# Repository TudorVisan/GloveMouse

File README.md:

GloveMouse
==========

GloveMouse repository

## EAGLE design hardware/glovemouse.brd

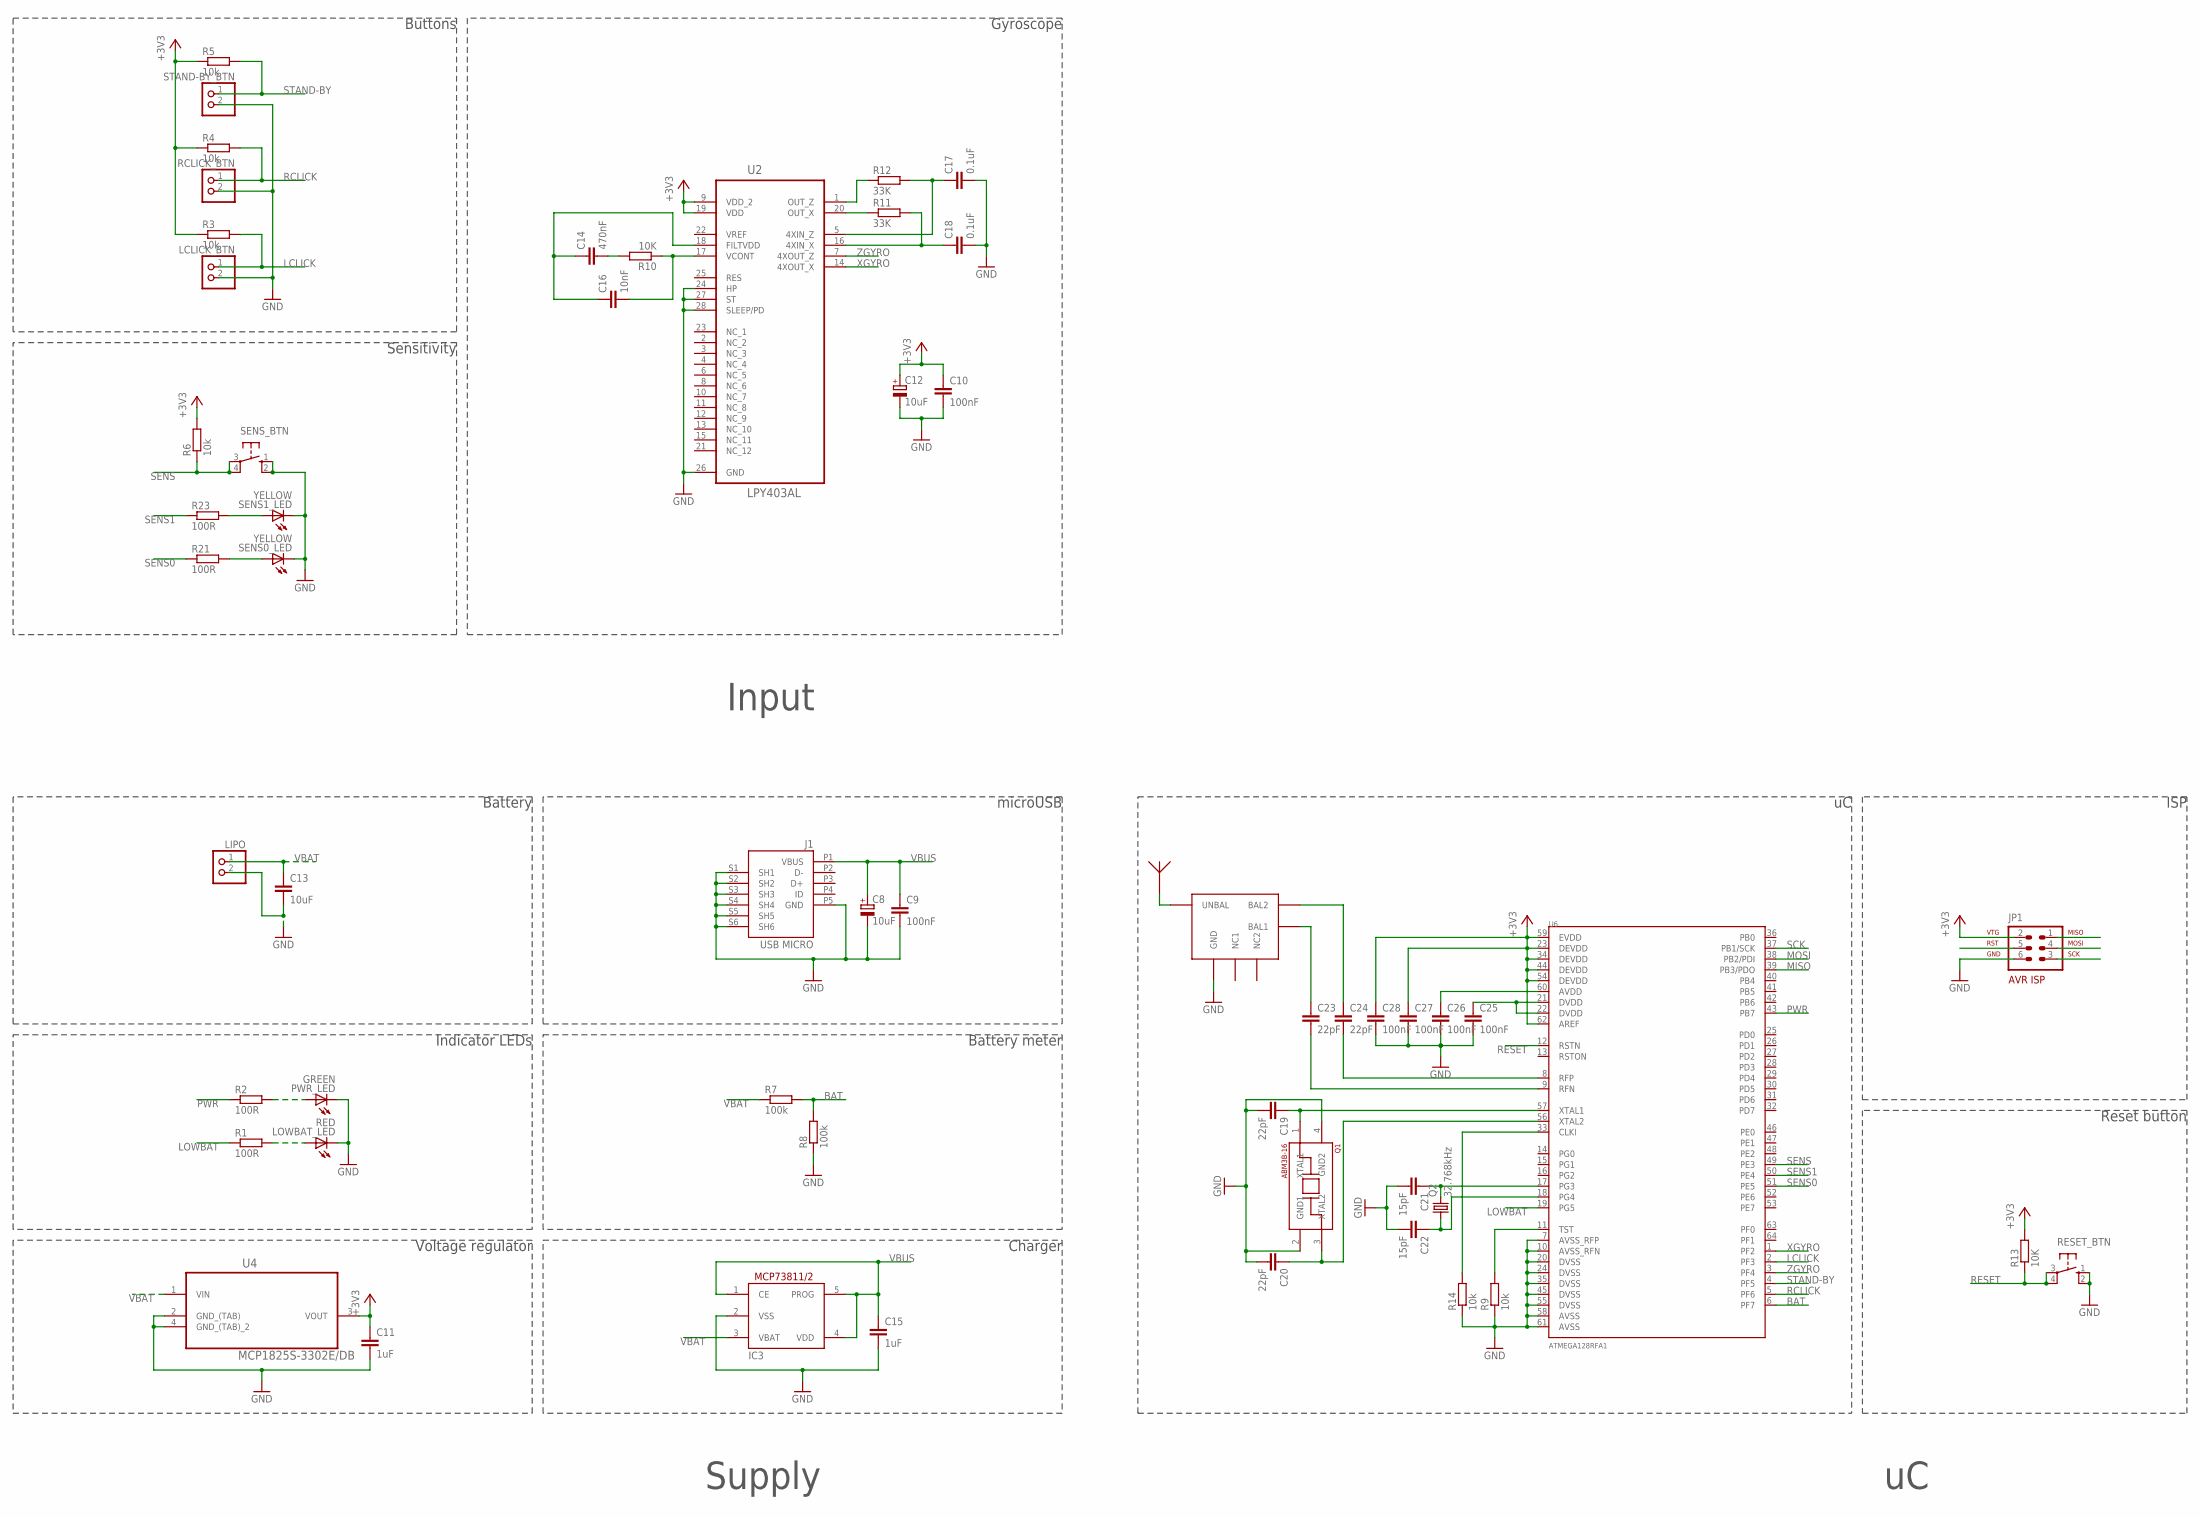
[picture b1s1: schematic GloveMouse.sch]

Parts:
C8, C12: 10uF; SMC_B
C9, C10: 100nF; C0603K
C11, C15: 1uF; C0603K
C13: 10uF; C0603K
C14: 470nF; C0603K
C16: 10nF; C0603K
C17, C18: 0.1uF; C0603K
C19, C20, C23, C24: 22pF; C0603
C21, C22: 15pF; C0603
C25, C26, C27, C28: 100nF; C0603
IC3: MCP73811/2; SOT23-5L
J1: USB MICRO; CON2_USB_MICRO_B_AT
JP1: AVR-ISP-6
LCLICK_BTN: PINHD-1X2/90; 1X02/90
LIPO: PINHD-1X2/90; 1X02/90
LOWBAT_LED: RED; CHIP-LED0805
PWR_LED: GREEN; CHIP-LED0805
Q1: ABM3B-16; ABM3B
Q2: 32.768kHz; FC-12M
R1, R2, R21, R23: 100R; R0603
R3, R4, R5, R6, R9, R14: 10k; R0603
R7, R8: 100k; R0603
R10, R13: 10K; R0603
R11, R12: 33K; R0603
RCLICK_BTN: PINHD-1X2/90; 1X02/90
RESET_BTN: 10-XX; B3F-10XX
SENS0_LED, SENS1_LED: YELLOW; CHIP-LED0805
SENS_BTN: 10-XX; B3F-10XX
STAND-BY_BTN: PINHD-1X2/90; 1X02/90
U2: LPY403AL; LGA28R50P8X6_500X400X100
U3: ANTENNA; ANTPACK
U4: MCP1825S-3302E/DB; SOT230P700X180-4N
U5: BALUN; BALPACK
U6: ATMEGA128RFA1; QFN-64

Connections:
+3V3: C10.1, C11.1, C12.+, C27.1, C28.1, JP1.2, R3.1, R4.1, R5.1, R6.2, R13.2, U2.9 (VDD_2), U2.19 (VDD), U4.3 (VOUT), U6.23 (DEVDD), U6.34 (DEVDD), U6.44 (DEVDD), U6.54 (DEVDD), U6.59 (EVDD), U6.62 (AREF)
BAT: R7.2, R8.2, U6.6 (PF7)
F1: C14.1, C16.1, U2.18 (FILTVDD)
F2: C16.2, R10.1, U2.17 (VCONT)
GND: C8.-, C9.2, C10.2, C11.2, C12.-, C13.2, C15.2, C17.2, C18.2, C19.2, C20.2, C21.2, C22.2, C25.2, C26.2, C27.2, C28.2, IC3.2 (VSS), J1.P5 (GND), J1.S1 (SH1), J1.S2 (SH2), J1.S3 (SH3), J1.S4 (SH4), J1.S5 (SH5), J1.S6 (SH6), JP1.6, LCLICK_BTN.2, LIPO.2, LOWBAT_LED.C, PWR_LED.C, Q1.2 (GND1), Q1.4 (GND2), R8.1, R9.1, R14.1, RCLICK_BTN.2, RESET_BTN.1 (S), RESET_BTN.2 (S1), SENS0_LED.C, SENS1_LED.C, SENS_BTN.1 (S), SENS_BTN.2 (S1), STAND-BY_BTN.2, U2.24 (HP), U2.26 (GND), U2.27 (ST), U2.28 (SLEEP/PD), U4.2 (GND_(TAB)), U4.4 (GND_(TAB)_2), U5.P$3 (GND), U6.7 (AVSS_RFP), U6.10 (AVSS_RFN), U6.20 (DVSS), U6.24 (DVSS), U6.35 (DVSS), U6.45 (DVSS), U6.55 (DVSS), U6.58 (AVSS), U6.61 (AVSS)
LCLICK: LCLICK_BTN.1, R3.2, U6.2 (PF3)
LOWBAT: R1.1, U6.19 (PG5)
MISO: JP1.1, U6.39 (PB3/PDO)
MOSI: JP1.4, U6.38 (PB2/PDI)
unnamed: R23.2, SENS1_LED.A
unnamed: LOWBAT_LED.A, R1.2
unnamed: PWR_LED.A, R2.2
unnamed: C14.2, R10.2
unnamed: R21.2, SENS0_LED.A
unnamed: R12.1, U2.1 (OUT_Z)
unnamed: R11.1, U2.20 (OUT_X)
unnamed: C20.1, Q1.3 (XTAL2), U6.56 (XTAL2)
unnamed: C19.1, Q1.1 (XTAL1), U6.57 (XTAL1)
unnamed: C18.1, R11.2, U2.16 (4XIN_X)
unnamed: C21.1, Q2.2, U6.17 (PG3)
unnamed: C22.1, Q2.1, U6.18 (PG4)
unnamed: C24.2, U6.8 (RFP)
unnamed: C23.2, U6.9 (RFN)
unnamed: C23.1, U5.P$4 (BAL1)
unnamed: C24.1, U5.P$6 (BAL2)
unnamed: C25.1, U6.21 (DVDD), U6.22 (DVDD)
unnamed: C26.1, U6.60 (AVDD)
unnamed: R9.2, U6.11 (TST)
unnamed: R14.2, U6.33 (CLKI)
unnamed: U3.P$1, U5.P$1 (UNBAL)
PWR: R2.1, U6.43 (PB7)
RCLICK: R4.2, RCLICK_BTN.1, U6.5 (PF6)
RESET: JP1.5, R13.1, RESET_BTN.3, RESET_BTN.4 (P1), U6.12 (RSTN)
SCK: JP1.3, U6.37 (PB1/SCK)
SENS: R6.1, SENS_BTN.3, SENS_BTN.4 (P1), U6.49 (PE3)
SENS0: R21.1, U6.51 (PE5)
SENS1: R23.1, U6.50 (PE4)
STAND-BY: R5.2, STAND-BY_BTN.1, U6.4 (PF5)
VBAT: C13.1, IC3.3 (VBAT), LIPO.1, R7.1, U4.1 (VIN)
VBUS: C8.+, C9.1, C15.1, IC3.1 (CE), IC3.4 (VDD), IC3.5 (PROG), J1.P1 (VBUS)
XGYRO: U2.14 (4XOUT_X), U6.1 (PF2)
XOUT-1X2: C17.1, R12.2, U2.5 (4XIN_Z)
ZGYRO: U2.7 (4XOUT_Z), U6.3 (PF4)

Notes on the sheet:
Voltage regulator
Battery
Charger
microUSB
Indicator LEDs
Battery meter
Supply
Input
Buttons
Sensitivity
Gyroscope
ISP
Reset button

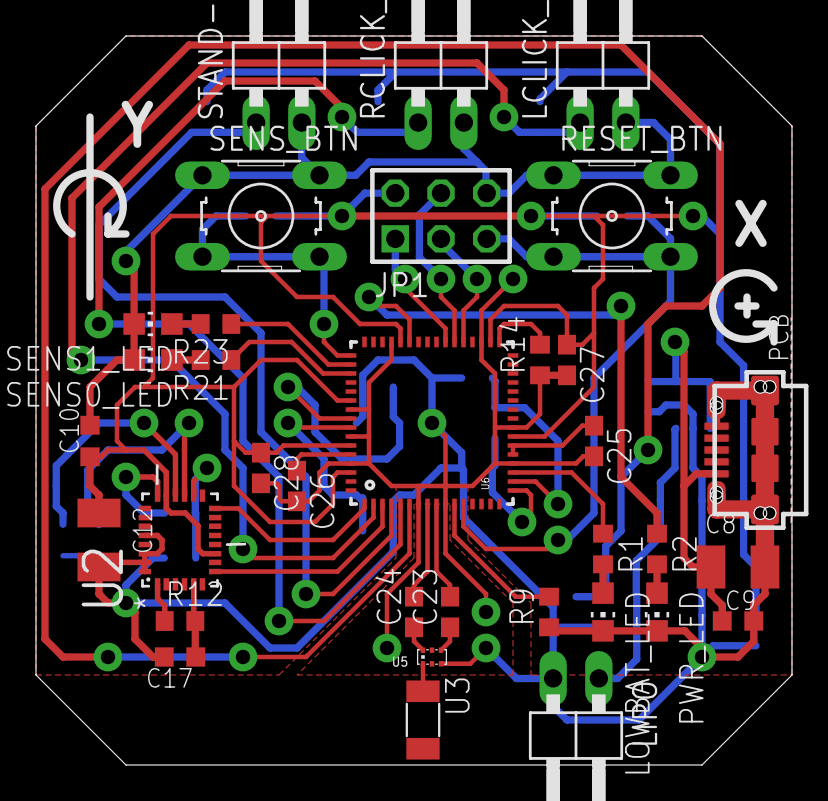
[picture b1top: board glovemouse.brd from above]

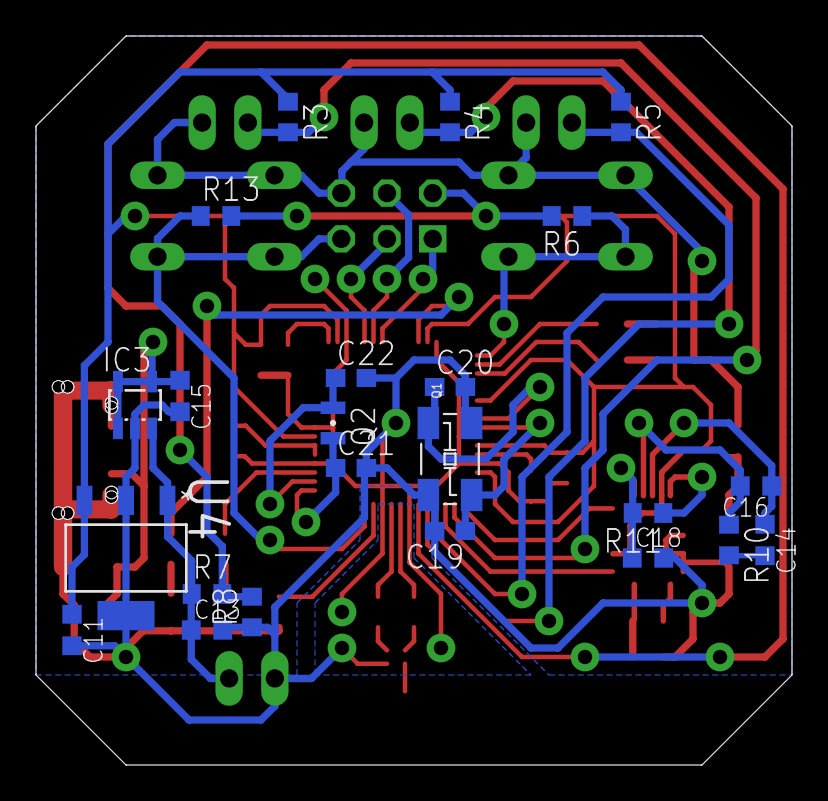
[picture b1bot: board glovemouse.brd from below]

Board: 2 copper layers, 42.0 x 40.5 mm, 57 parts (23 on the bottom side), 43 nets.

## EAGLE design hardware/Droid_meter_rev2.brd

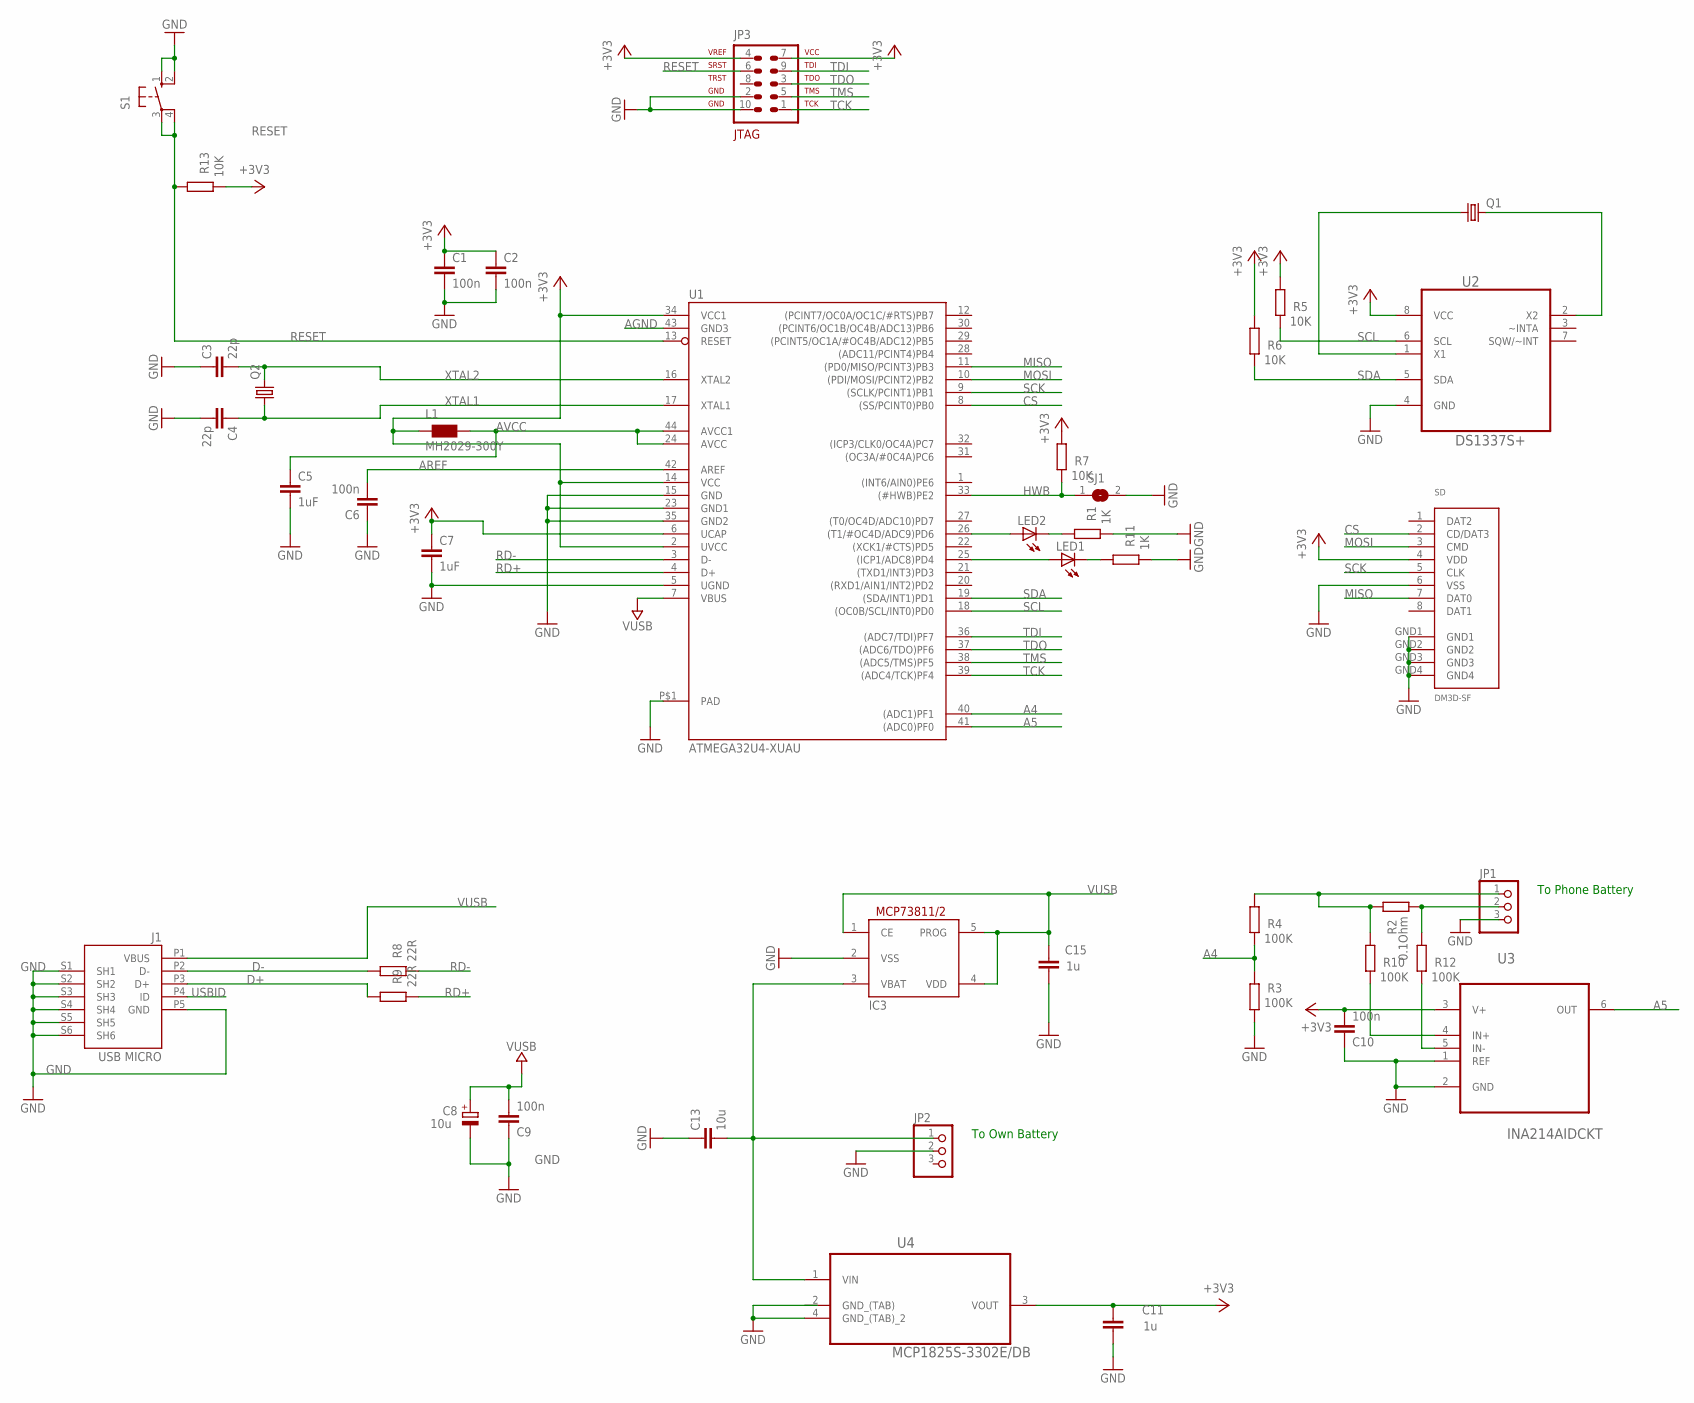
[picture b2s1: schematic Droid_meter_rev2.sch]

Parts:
C1, C2, C6, C9, C10: 100n; C0603-ROUND
C3, C4: 22p; C0603-ROUND
C5, C7: 1uF; C0603-ROUND
C8: 10u; SMC_B
C11, C15: 1u; C0603-ROUND
C13: 10u; C0805
IC3: MCP73811/2; SOT23-5L
J1: USB MICRO; CON2_USB_MICRO_B_AT
JP1, JP2: PINHD-1X3; 1X03
JP3: AVR-JTAG-10
L1: MH2029-300Y; 0805
LED1, LED2: LEDCHIP-LED0603; CHIP-LED0603
Q1: CRYSTALMM39SL; MM39SL
Q2: CRYSTALCTS406; CTS406
R1, R11: 1K; R0603-ROUND
R2: 0.1Ohm; R2512
R3, R4, R10, R12: 100K; R0603-ROUND
R5, R6, R7, R13: 10K; R0603-ROUND
R8, R9: 22R; R0603-ROUND
S1: 10-XX; B3F-10XX
SD: DM3D-SF
SJ1: SJ
U1: ATMEGA32U4-XUAU; TQFP44-PAD
U2: DS1337S+; SOIC127P600X175-8N
U3: INA214AIDCKT; SOT65P210X110-6N
U4: MCP1825S-3302E/DB; SOT230P700X180-4N

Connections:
+3V3: C1.1, C2.1, C7.1, C10.2, C11.2, JP3.4, JP3.7, L1.1, R5.1, R6.1, R7.1, R13.2, SD.4 (VDD), U1.2 (UVCC), U1.6 (UCAP), U1.14 (VCC), U1.34 (VCC1), U2.8 (VCC), U3.3 (V+), U4.3 (VOUT)
A4: R3.1, R4.2, U1.40 ((ADC1)PF1)
A5: U1.41 ((ADC0)PF0), U3.6 (OUT)
AGND: U1.43 (GND3)
AREF: C6.2, U1.42 (AREF)
AVCC: C5.1, L1.2, U1.24 (AVCC), U1.44 (AVCC1)
CS: SD.2 (CD/DAT3), U1.8 ((SS/PCINT0)PB0)
D+: J1.P3 (D+), R9.1
D-: J1.P2 (D-), R8.1
GND: C1.2, C2.2, C3.1, C4.2, C5.2, C6.1, C7.2, C8.-, C9.1, C10.1, C11.1, C13.1, C15.1, IC3.2 (VSS), J1.P5 (GND), J1.S1 (SH1), J1.S2 (SH2), J1.S3 (SH3), J1.S4 (SH4), J1.S5 (SH5), J1.S6 (SH6), JP1.3, JP2.2, JP3.2, JP3.10, R1.2, R3.2, R11.2, S1.1 (S), S1.2 (S1), SD.6 (VSS), SD.GND1, SD.GND2, SD.GND3, SD.GND4, SJ1.2, U1.5 (UGND), U1.15 (GND), U1.23 (GND1), U1.35 (GND2), U1.P$1 (PAD), U2.4 (GND), U3.1 (REF), U3.2 (GND), U4.4 (GND_(TAB)_2)
HWB: R7.2, SJ1.1, U1.33 ((#HWB)PE2)
MISO: SD.7 (DAT0), U1.11 ((PD0/MISO/PCINT3)PB3)
MOSI: SD.3 (CMD), U1.10 ((PDI/MOSI/PCINT2)PB2)
unnamed: JP1.1, R2.2, R4.1, R10.1
unnamed: JP1.2, R2.1, R12.1
unnamed: Q1.4 (2), U2.2 (X2)
unnamed: Q1.1, U2.1 (X1)
unnamed: C13.2, IC3.3 (VBAT), JP2.1, U4.1 (VIN)
unnamed: R10.2, U3.4 (IN+)
unnamed: LED2.C, R1.1
unnamed: LED1.C, R11.1
unnamed: R12.2, U3.5 (IN-)
unnamed: LED1.A, U1.25 ((ICP1/ADC8)PD4)
unnamed: LED2.A, U1.26 ((T1/#OC4D/ADC9)PD6)
RD+: R9.2, U1.4 (D+)
RD-: R8.2, U1.3 (D-)
RESET: JP3.6, R13.1, S1.3, S1.4 (P1), U1.13 (RESET)
SCK: SD.5 (CLK), U1.9 ((SCLK/PCINT1)PB1)
SCL: R5.2, U1.18 ((OC0B/SCL/INT0)PD0), U2.6 (SCL)
SDA: R6.2, U1.19 ((SDA/INT1)PD1), U2.5 (SDA)
TCK: JP3.1, U1.39 ((ADC4/TCK)PF4)
TDI: JP3.9, U1.36 ((ADC7/TDI)PF7)
TDO: JP3.3, U1.37 ((ADC6/TDO)PF6)
TMS: JP3.5, U1.38 ((ADC5/TMS)PF5)
USBID: J1.P4 (ID)
VUSB: C8.+, C9.2, C15.2, IC3.1 (CE), IC3.4 (VDD), IC3.5 (PROG), J1.P1 (VBUS), U1.7 (VBUS)
XTAL1: C4.1, Q2.1, U1.17 (XTAL1)
XTAL2: C3.2, Q2.3 (2), U1.16 (XTAL2)

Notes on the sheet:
To Phone Battery
To Own Battery

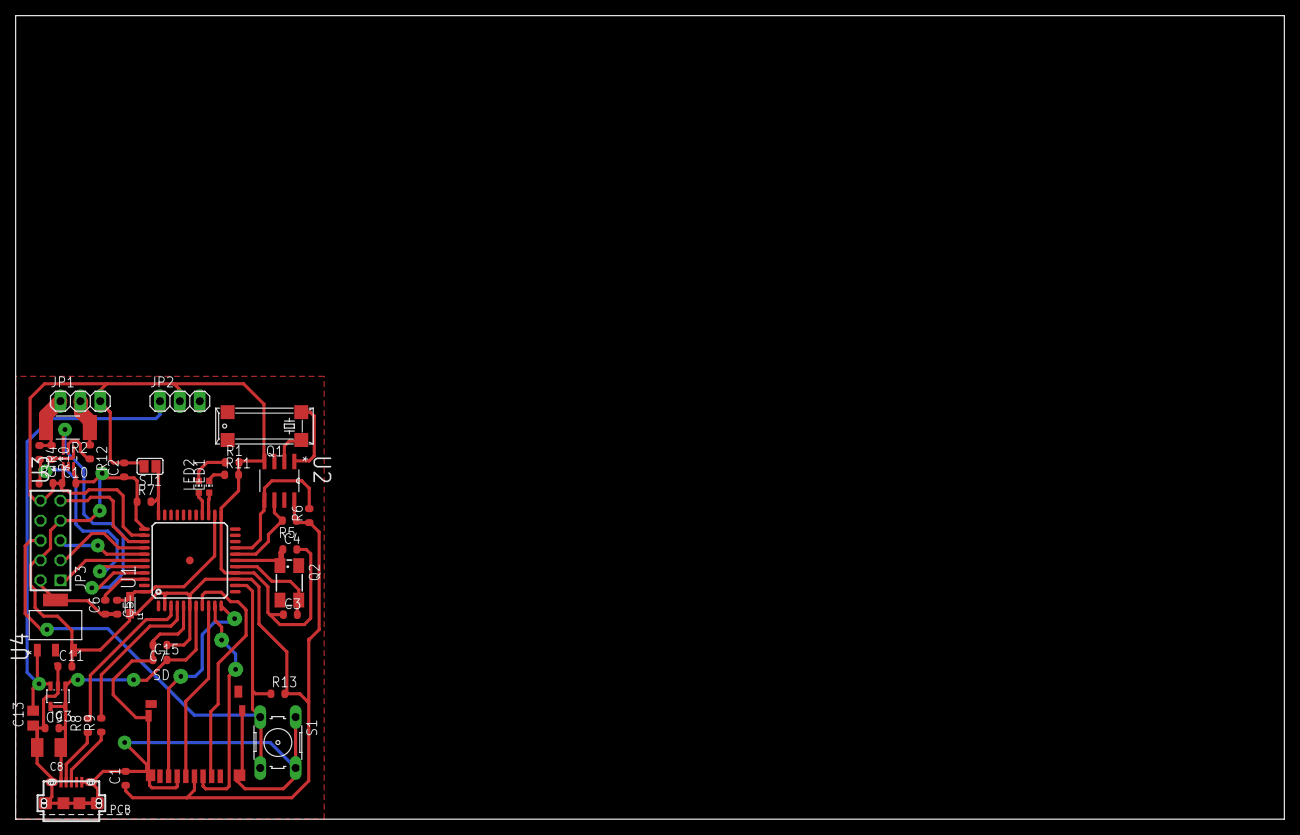
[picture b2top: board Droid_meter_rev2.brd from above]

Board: 2 copper layers, 161.9 x 102.5 mm, 43 parts (0 on the bottom side), 36 nets.

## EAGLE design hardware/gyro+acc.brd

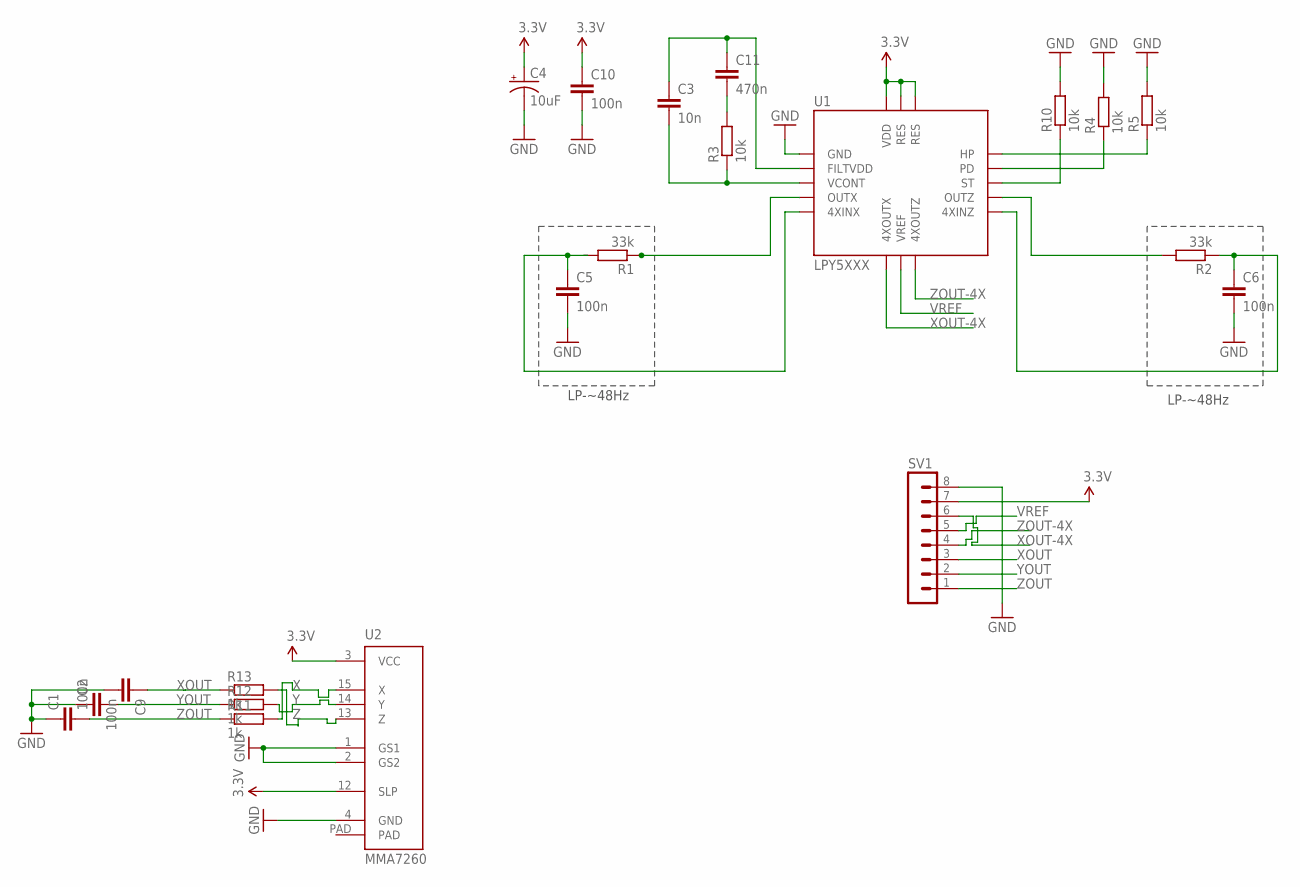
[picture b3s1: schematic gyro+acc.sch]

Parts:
C1, C5, C6, C9, C10: 100n; C1206
C2: C-EUC1206; C1206
C3: 10n; C1206
C4: 10uF; EIA3216
C11: 470n; C1206
R1, R2: 33k; M1206
R3, R4, R5, R10: 10k; M1206
R11, R12, R13: 1k; M1206
SV1: MA08-1
U1: LPY5XXX; ST-GYRO
U2: MMA7260

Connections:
3.3V: C4.A (+), C10.1, SV1.7, U1.14 (RES), U1.15 (RES), U1.16 (VDD), U2.3 (VCC), U2.12 (SLP)
F1: C3.1, C11.1, U1.2 (FILTVDD)
F2: C3.2, R3.1, U1.3 (VCONT)
GND: C1.1, C2.1, C4.C (-), C5.2, C6.2, C9.2, C10.2, R4.2, R5.2, R10.2, SV1.8, U1.1 (GND), U2.1 (GS1), U2.2 (GS2), U2.4 (GND)
HP: R5.1, U1.13 (HP)
unnamed: R1.1, U1.4 (OUTX)
unnamed: C11.2, R3.2
unnamed: R2.2, U1.10 (OUTZ)
PD: R4.1, U1.12 (PD)
ST: R10.1, U1.11 (ST)
VREF: SV1.5, U1.7 (VREF)
X: R11.2, U2.15 (X)
XOUT: C9.1, R13.1, SV1.3
XOUT-1X: C5.1, R1.2, U1.5 (4XINX)
XOUT-4X: SV1.6, U1.6 (4XOUTX)
Y: R12.2, U2.14 (Y)
YOUT: C2.2, R12.1, SV1.2
Z: R13.2, U2.13 (Z)
ZOUT: C1.2, R11.1, SV1.1
ZOUT-1X: C6.1, R2.1, U1.9 (4XINZ)
ZOUT-4X: SV1.4, U1.8 (4XOUTZ)

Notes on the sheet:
LP-~48Hz

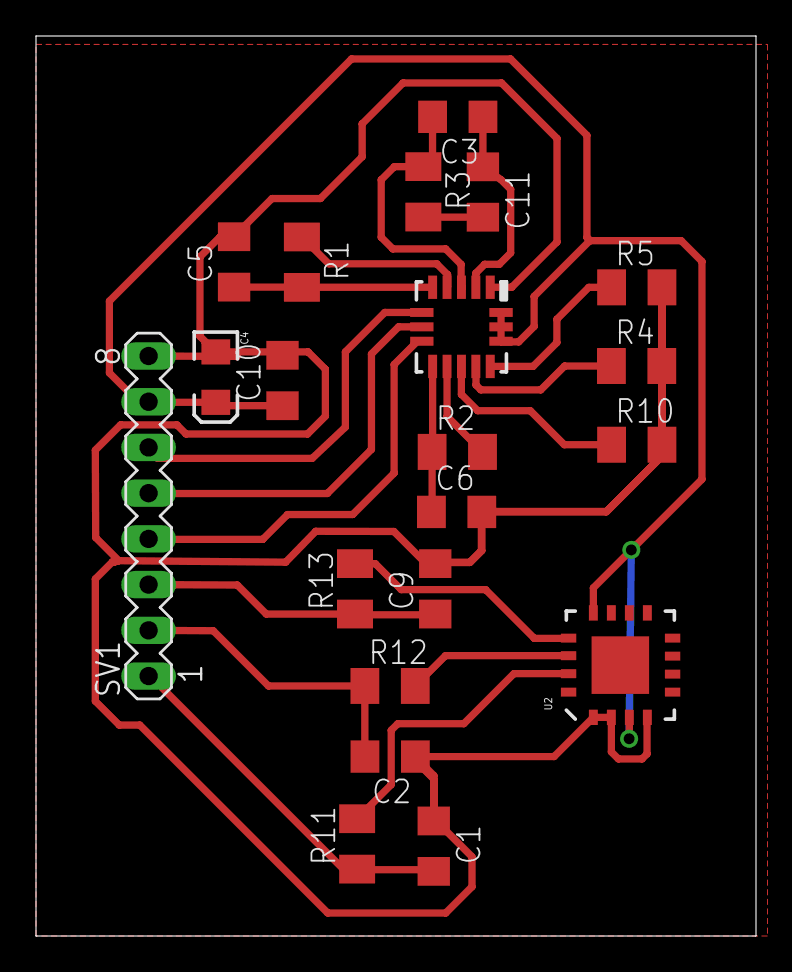
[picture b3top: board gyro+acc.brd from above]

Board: 2 copper layers, 40.0 x 50.0 mm, 21 parts (0 on the bottom side), 21 nets.

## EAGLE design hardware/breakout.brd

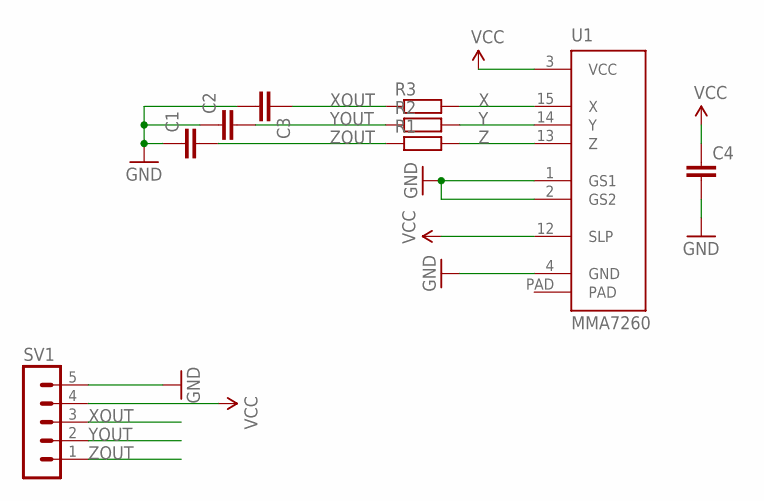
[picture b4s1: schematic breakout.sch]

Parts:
C1, C2, C3, C4: C-EUC1206; C1206
R1, R2, R3: R-EU_R1206; R1206
SV1: MA05-1
U1: MMA7260

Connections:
GND: C1.1, C2.1, C3.2, C4.2, SV1.5, U1.1 (GS1), U1.2 (GS2), U1.4 (GND)
VCC: C4.1, SV1.4, U1.3 (VCC), U1.12 (SLP)
X: R3.2, U1.15 (X)
XOUT: C3.1, R3.1, SV1.3
Y: R2.2, U1.14 (Y)
YOUT: C2.2, R2.1, SV1.2
Z: R1.2, U1.13 (Z)
ZOUT: C1.2, R1.1, SV1.1

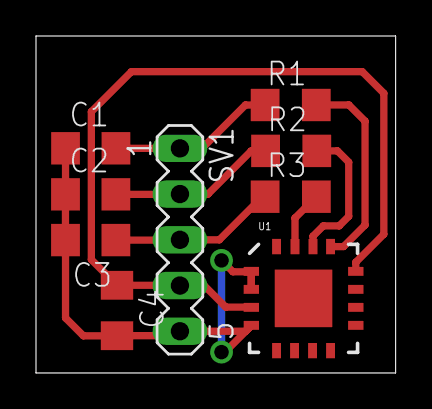
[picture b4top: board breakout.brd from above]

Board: 2 copper layers, 20.0 x 18.7 mm, 9 parts (0 on the bottom side), 8 nets.

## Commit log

2014-06-13 GloveMouse v1.0 all-in-one commit
2014-06-13 GloveMouse v2.0 all-in-one commit
2014-06-13 GloveMouse v2.1 all-in-one commit
2014-06-13 GloveMouse v2.2 all-in-one commit
2014-06-13 GloveMouse v2.3 all-in-one commit
2014-06-13 GloveMouse v2.4 all-in-one commit
2014-06-20 v3.0: initial commit for GloveMouse v3.0
    Changed ATmega32U4 with ATmega128RFA1.
    Added onboard gyroscope from v2.4.
    Added battery level measuring system.
    Added controlable power led and low-battery led.
2014-06-20 v3.0 release candidate 1
    Changed secondary crystal.
    Finished routing.
2014-06-20 v3.0 release candidate 2
    Changed grounding for ATmega128RFA1 so that it doesn't pass through antenna
    ground plane.
2014-06-20 v3.0 release candidate 3
    Changed grounding for antenna.
2014-07-14 v3.0 cleanup
    Did some cleaning and tidying up.
